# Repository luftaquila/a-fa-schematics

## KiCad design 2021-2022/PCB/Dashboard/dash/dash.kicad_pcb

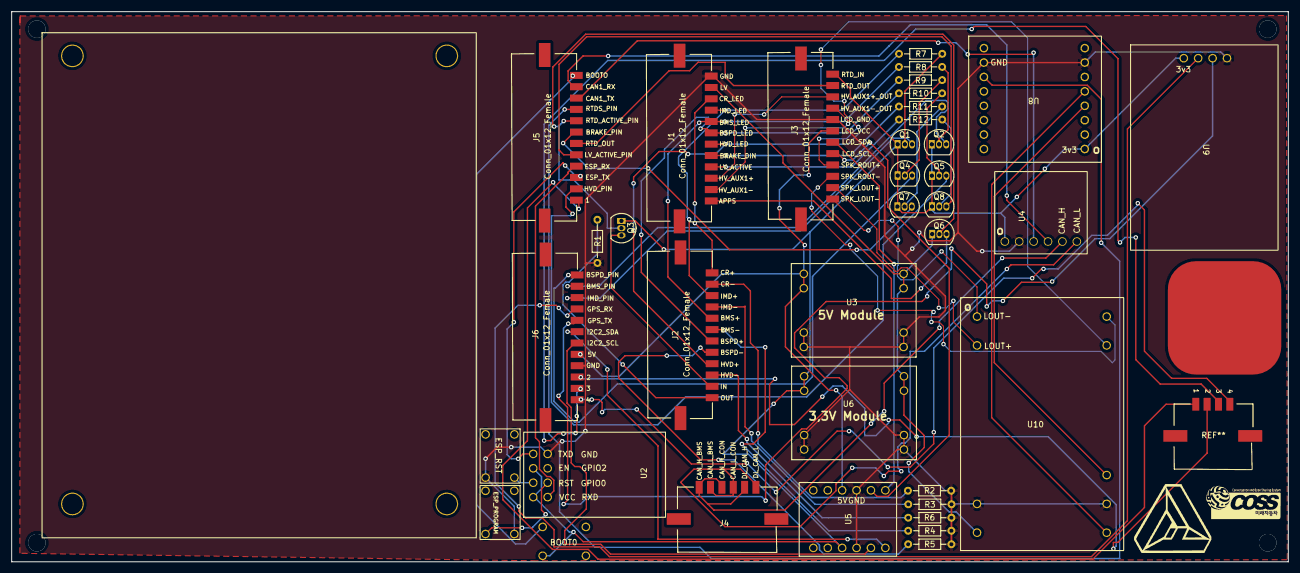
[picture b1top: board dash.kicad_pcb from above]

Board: 2 copper layers, 225.1 x 97.0 mm, 37 parts (0 on the bottom side), 56 nets.

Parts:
BOOT0: ESP_PROGRAM; butttttttttttttt
ESP_PROGRAM: ESP_PROGRAM; butttttttttttttt
ESP_RST: ESP_RST; butttttttttttttt
J1, J2, J3, J5, J6: Conn_01x12_Female; 5600201220
J4: Conn_01x06_Female; 6pin dura
Q1, Q2, Q3, Q4, Q5, Q6, Q7, Q8: 2N3904; TO-92_Inline
R1: 100; R_Axial_DIN0204_L3.6mm_D1.6mm_P7.62mm_Horizontal
R2, R3, R4, R5: 1k; R_Axial_DIN0204_L3.6mm_D1.6mm_P7.62mm_Horizontal
R6, R7, R8, R9, R10, R11, R12: 10k; R_Axial_DIN0204_L3.6mm_D1.6mm_P7.62mm_Horizontal
U2: ESP8266
U3, U6: DCDC_Module; DC CONVERTER
U4: CAN_TRANSCEIVER; SZH-EKBG-030
U5: LOGIC_LEVEL_CONVERTER; Logic Level Converter
U8: DFR0299
U9: NEO-7M
U10: D302; AUDIOIO

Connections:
3V3: BOOT0.1 (A), J3.1, Q1.1 (E), Q2.1 (E), Q3.1 (E), Q4.1 (E), Q5.1 (E), Q7.1 (E), Q8.1 (E), U2.1, U4.1, U5.1, U6.1 (VOUT+), U6.2 (VOUT+), U8.1, U9.1
5V: J3.6, J6.8, U3.1 (VOUT+), U3.2 (VOUT+), U5.1
-: J2.12, R1.2
APPS: J1.12, Q6.3 (C)
BMS-: J2.6, R4.1
BMS_IN: J1.5, J2.5, R8.1
BMS_Pin: J6.2, Q2.3 (C)
BOOT0: BOOT0.2 (B), J5.1
BRAKE_DIN: J1.8, R11.1
BRAKE_Pin: J5.6, Q7.3 (C)
BSPD-: J2.8, R5.1
BSPD_IN: J1.6, J2.7, R9.1
BSPD_Pin: J6.1, Q4.3 (C)
CAN1_RX: J5.2, U4.1
CAN1_TX: J5.3, U4.1
CAN_H: J4.1, J4.3, J4.5, U4.1
CAN_L: J4.2, J4.4, J4.6, U4.1
CR-: J2.2, R2.1
CRITICAL_LED: J1.3, J2.1
ESP_RX: J5.9, U2.1
ESP_TX: J5.10, U2.1
GND: ESP_PROGRAM.1 (A), ESP_RST.2 (B), J1.1, J3.5, J6.9, R1.1, R2.2, R3.2, R4.2, R5.2, R6.2, U2.1, U3.3 (VOUT-), U3.4 (VOUT-), U3.5 (VIN-), U3.6 (VIN-), U4.1, U5.1, U6.3 (VOUT-), U6.4 (VOUT-), U6.5 (VIN-), U6.6 (VIN-), U8.1, U9.1, U10.1
GPS_RX: J6.4, U9.1
GPS_TX: J6.5, U9.1
HVD-: J2.10, R6.1
HVD_IN: J1.7, J2.9, R10.1
HVD_Pin: J5.11, Q5.3 (C)
HV_AUX1+: J1.10, J3.3
HV_AUX1-: J1.11, J3.4
I2C2_SCL: J6.7, U5.1
I2C2_SDA: J6.6, U5.1
IMD-: J2.4, R3.1
IMD_IN: J1.4, J2.3, R7.1
IMD_Pin: J6.3, Q1.3 (C)
IN: J2.11, Q3.3 (C)
LCD_SCL: J3.8, U5.1
LCD_SDA: J3.7, U5.1
LIN: U8.1, U10.1
LOUT+: J3.11, U10.1
LOUT-: J3.12, U10.1
LV: J1.2, Q6.1 (E), U3.7 (VIN+), U3.8 (VIN+), U6.7 (VIN+), U6.8 (VIN+), U10.1
LV_ACTIVE: J1.9, R12.1
LV_ACTIVE_Pin: J5.8, Q8.3 (C)
unnamed: Q1.2 (B), R7.2
unnamed: Q2.2 (B), R8.2
unnamed: Q4.2 (B), R9.2
unnamed: Q5.2 (B), R10.2
unnamed: Q7.2 (B), R11.2
unnamed: Q8.2 (B), R12.2
unnamed: ESP_RST.1 (A), U2.1
unnamed: ESP_PROGRAM.2 (B), U2.1
RIN: U8.1, U10.1
ROUT+: J3.9, U10.1
ROUT-: J3.10, U10.1
RTDS: J5.4, U8.1
RTD_ACTIVE_Pin: J5.5, Q3.2 (B), Q6.2 (B)
RTD_OUT: J3.2, J5.7

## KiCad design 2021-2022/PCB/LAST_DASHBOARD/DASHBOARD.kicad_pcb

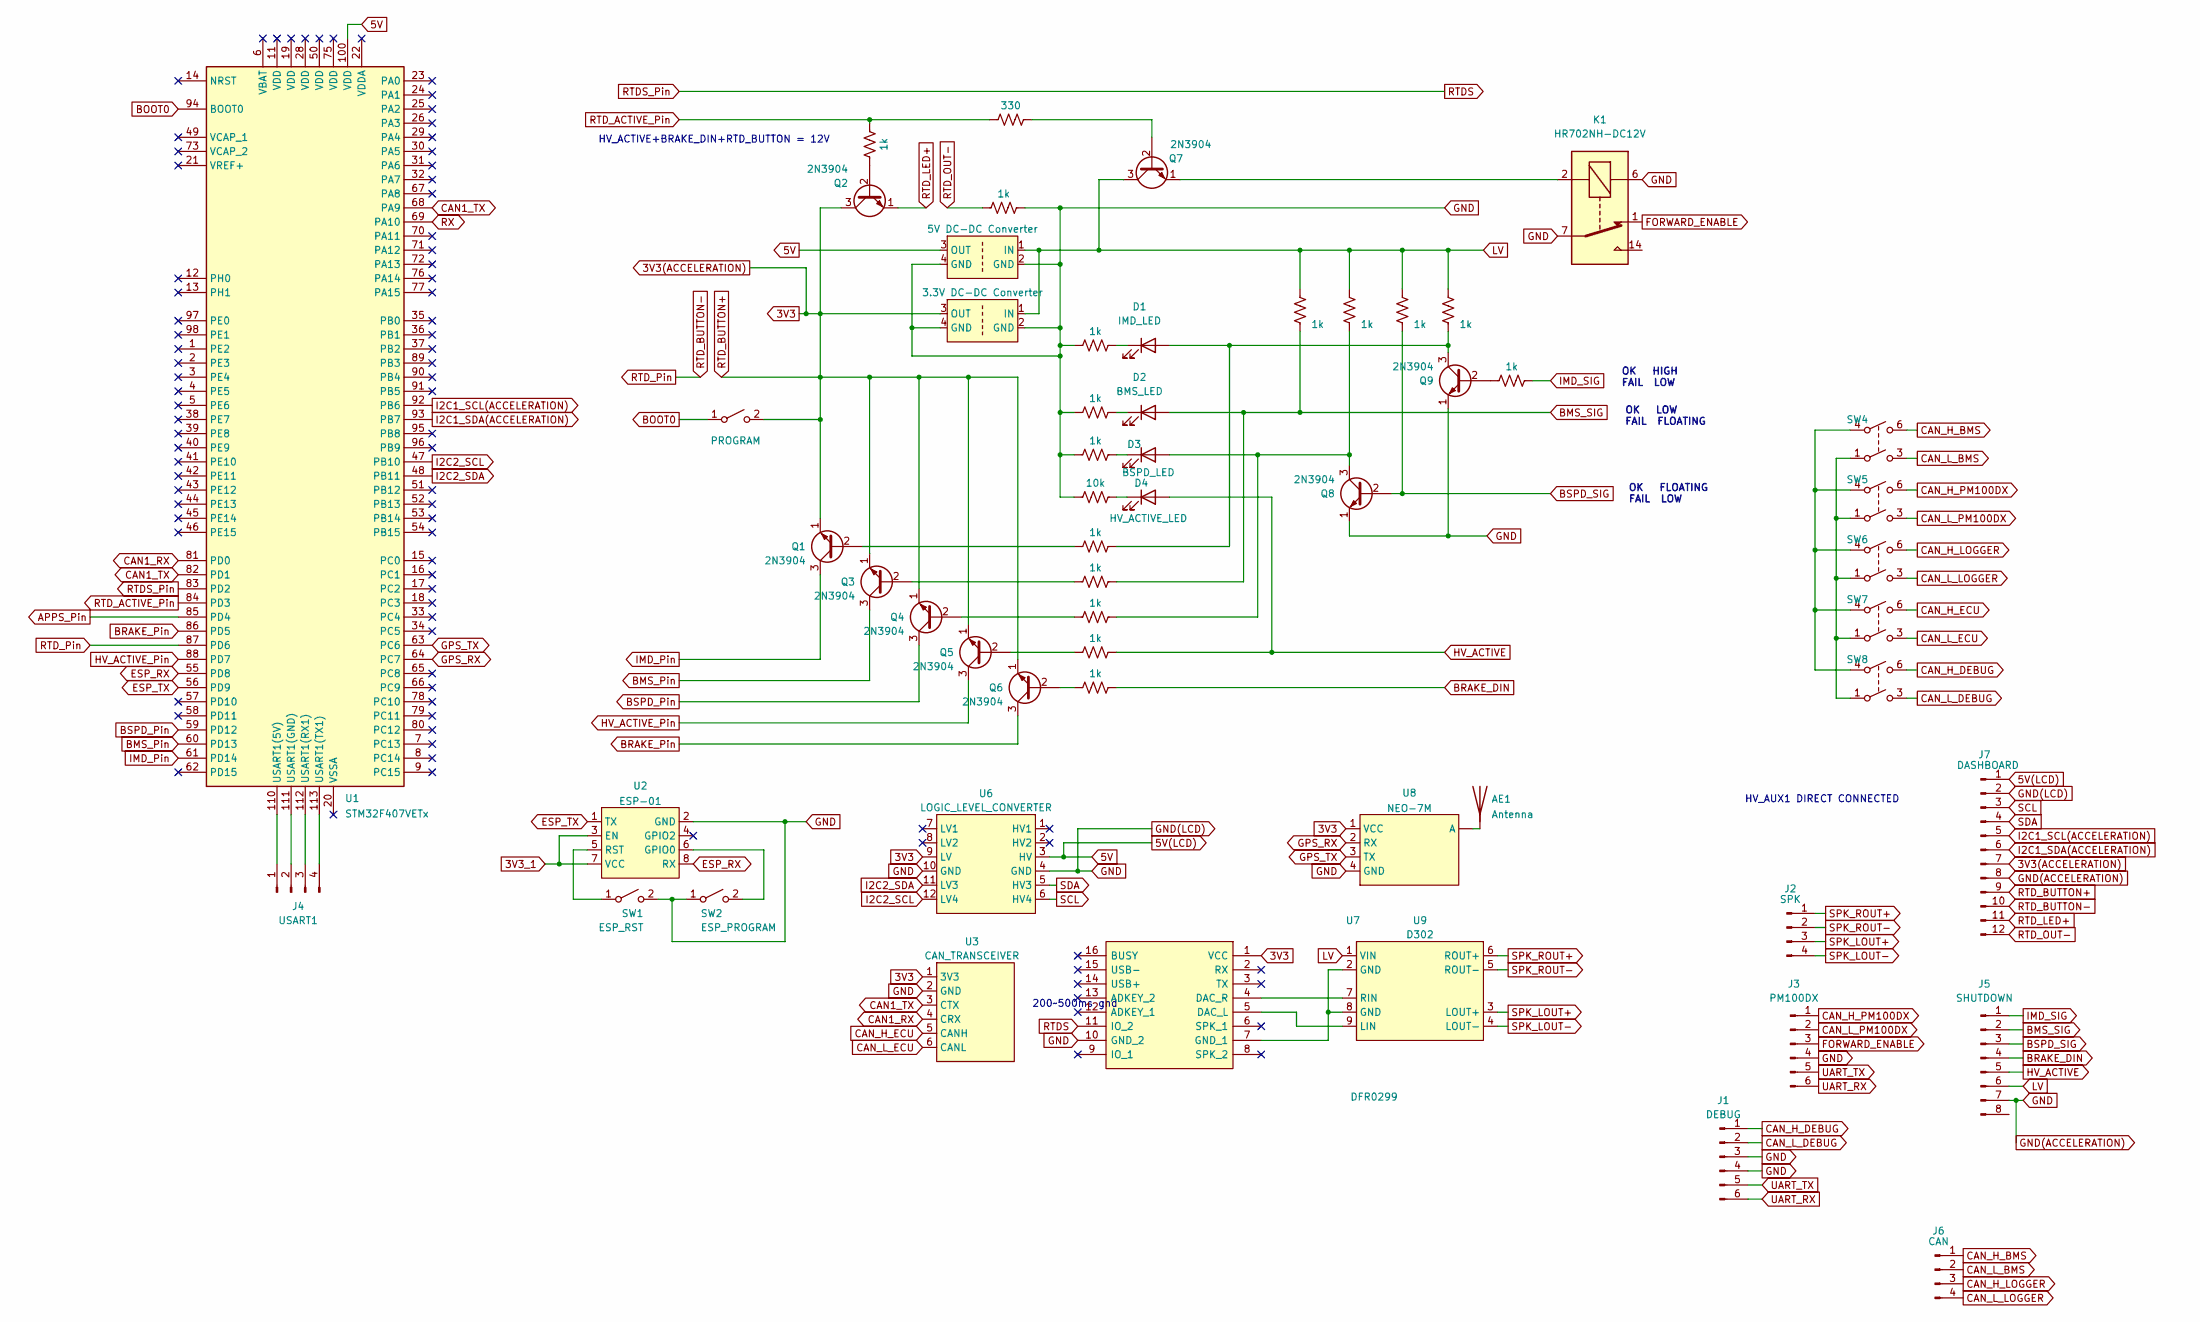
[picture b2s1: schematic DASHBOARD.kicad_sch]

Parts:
AE1: Antenna; ANTENA
D1: IMD_LED; LED_D5.0mm
D2: BMS_LED; LED_D5.0mm
D3: BSPD_LED; LED_D5.0mm
D4: HV_ACTIVE_LED; LED_D5.0mm
J1: DEBUG; PinHeader_1x06_P2.54mm_Vertical
J2: SPK; PinHeader_1x04_P2.54mm_Vertical
J3: PM100DX; PinHeader_1x06_P2.54mm_Vertical
J4: USART1; PinHeader_1x04_P2.54mm_Vertical
J5: SHUTDOWN; PinHeader_1x08_P2.54mm_Vertical
J6: CAN; PinHeader_1x04_P2.54mm_Vertical
J7: DASHBOARD; PinHeader_1x12_P2.54mm_Vertical
K1: HR702NH-DC12V
Q1, Q2, Q3, Q4, Q5, Q6, Q7, Q8, Q9: 2N3904; TO-92_Inline_Wide
R1, R2, R4, R5, R6, R8, R9, R10, R11, R12, R13, R14, R15, R16, R17: 1k; R_Axial_DIN0207_L6.3mm_D2.5mm_P10.16mm_Horizontal
R3: 330; R_Axial_DIN0207_L6.3mm_D2.5mm_P10.16mm_Horizontal
R7: 10k; R_Axial_DIN0207_L6.3mm_D2.5mm_P10.16mm_Horizontal
SW1: ESP_RST; TACT_SWITCH
SW2: ESP_PROGRAM; TACT_SWITCH
SW3: PROGRAM; TACT_SWITCH
SW4, SW5, SW6, SW7, SW8: SW_DPST; TOGGLE_SWITCH
U1: STM32F407VETx; STM32F407_HOLDER
U2: ESP-01; ESP01
U3: CAN_TRANSCEIVER; CAN_TRANSIVER
U4: 5V DC-DC Converter; DCDC_MODULE
U5: 3.3V DC-DC Converter; DCDC_MODULE
U6: LOGIC_LEVEL_CONVERTER
U7: DFR0299; Manufacturer_Part_Number DFR0299; Mouser Part Number 426-DFR0299
U8: NEO-7M; GPSV3-NE0
U9: D302; SFT-D302

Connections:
3V3: J7.7, J7.9, Q1.1 (E), Q2.3 (C), Q3.1 (E), Q4.1 (E), Q5.1 (E), Q6.1 (E), SW3.2 (B), U3.1 (3V3), U5.3 (OUT), U6.9 (LV), U7.1 (VCC), U8.1 (VCC)
3V3_1: U2.3 (EN), U2.7 (VCC)
5V: J7.1, U1.100 (VDD), U4.3 (OUT), U6.3 (HV)
APPS_Pin: U1.85 (PD4)
BMS_Pin: Q3.3 (C), U1.60 (PD13)
BMS_SIG: D2.2 (A), J5.2, R9.1, R13.2
BOOT0: SW3.1 (A), U1.94 (BOOT0)
BRAKE_DIN: J5.4, R12.1
BRAKE_Pin: Q6.3 (C), U1.86 (PD5)
BSPD_Pin: Q4.3 (C), U1.59 (PD12)
BSPD_SIG: J5.3, Q8.2 (B), R15.2
CAN1_RX: U1.81 (PD0), U3.4 (CRX)
CAN1_TX: U1.68 (PA9), U1.82 (PD1), U3.3 (CTX)
CAN_H_BMS: J6.1, SW4.6
CAN_H_DEBUG: J1.1, SW8.6
CAN_H_ECU: SW7.6, U3.5 (CANH)
CAN_H_LOGGER: J6.3, SW6.6
CAN_H_PM100DX: J3.1, SW5.6
CAN_L_BMS: J6.2, SW4.3
CAN_L_DEBUG: J1.2, SW8.3
CAN_L_ECU: SW7.3, U3.6 (CANL)
CAN_L_LOGGER: J6.4, SW6.3
CAN_L_PM100DX: J3.2, SW5.3
ESP_RX: U1.55 (PD8), U2.8 (RX)
ESP_TX: U1.56 (PD9), U2.1 (TX)
FORWARD_ENABLE: J3.3, K1.1
GND: J1.3, J1.4, J3.4, J5.7, J7.2, J7.8, K1.6, K1.7, K1.8, Q8.1 (E), Q9.1 (E), R2.1, R4.2, R5.2, R6.2, R7.2, SW1.2 (B), SW2.1 (A), U2.2 (GND), U3.2 (GND), U4.2 (GND), U4.4 (GND), U5.2 (GND), U5.4 (GND), U6.4 (GND), U6.10 (GND), U7.10 (GND_2), U8.4 (GND)
GPS_RX: U1.64 (PC7), U8.2 (RX)
GPS_TX: U1.63 (PC6), U8.3 (TX)
HV_ACTIVE: D4.2 (A), J5.5, R11.1
HV_ACTIVE_Pin: Q5.3 (C), U1.88 (PD7)
I2C1_SCL(ACCELERATION): J7.5, U1.92 (PB6)
I2C1_SDA(ACCELERATION): J7.6, U1.93 (PB7)
I2C2_SCL: U1.47 (PB10), U6.12 (LV4)
I2C2_SDA: U1.48 (PB11), U6.11 (LV3)
IMD_Pin: Q1.3 (C), U1.61 (PD14)
IMD_SIG: J5.1, R17.1
LV: J5.6, Q7.3 (C), R13.1, R14.1, R15.1, R16.1, U4.1 (IN), U5.1 (IN), U9.1 (VIN)
unnamed: AE1.1 (A), U8. (A)
unnamed: D1.1 (K), R4.1
unnamed: D1.2 (A), Q9.3 (C), R8.1, R16.2
unnamed: D2.1 (K), R5.1
unnamed: D3.1 (K), R6.1
unnamed: D3.2 (A), Q8.3 (C), R10.1, R14.2
unnamed: D4.1 (K), R7.1
unnamed: J4.1, U1.110 (USART1(5V))
unnamed: J4.2, U1.111 (USART1(GND))
unnamed: J4.3, U1.112 (USART1(RX1))
unnamed: J4.4, U1.113 (USART1(TX1))
unnamed: K1.2, Q7.1 (E)
unnamed: Q1.2 (B), R8.2
unnamed: Q2.2 (B), R1.1
unnamed: Q3.2 (B), R9.2
unnamed: Q4.2 (B), R10.2
unnamed: Q5.2 (B), R11.2
unnamed: Q6.2 (B), R12.2
unnamed: Q7.2 (B), R3.1
unnamed: Q9.2 (B), R17.2
unnamed: SW1.1 (A), U2.5 (RST)
unnamed: SW2.2 (B), U2.6 (GPIO0)
unnamed: SW4.1, SW5.1, SW6.1, SW7.1, SW8.1
unnamed: SW4.4, SW5.4, SW6.4, SW7.4, SW8.4
unnamed: U7.4 (DAC_R), U9.7 (RIN)
unnamed: U7.5 (DAC_L), U9.9 (LIN)
unnamed: U7.7 (GND_1), U9.2 (GND), U9.8 (GND)
RTDS: U1.83 (PD2), U7.11 (IO_2)
RTD_ACTIVE_Pin: R1.2, R3.2, U1.84 (PD3)
RTD_BUTTON-: J7.10, U1.87 (PD6)
RTD_LED+: J7.11, Q2.1 (E)
RTD_OUT-: J7.12, R2.2
RX: U1.69 (PA10)
SCL: J7.3, U6.6 (HV4)
SDA: J7.4, U6.5 (HV3)
SPK_LOUT+: J2.3, U9.3 (LOUT+)
SPK_LOUT-: J2.4, U9.4 (LOUT-)
SPK_ROUT+: J2.1, U9.6 (ROUT+)
SPK_ROUT-: J2.2, U9.5 (ROUT-)
UART_RX: J1.6, J3.6
UART_TX: J1.5, J3.5

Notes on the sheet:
OK HIGH FAIL LOW
HV_AUX1 DIRECT CONNECTED
200~500ms gnd
HV_ACTIVE+BRAKE_DIN+RTD_BUTTON = 12V
OK LOW FAIL FLOATING
OK FLOATING FAIL LOW

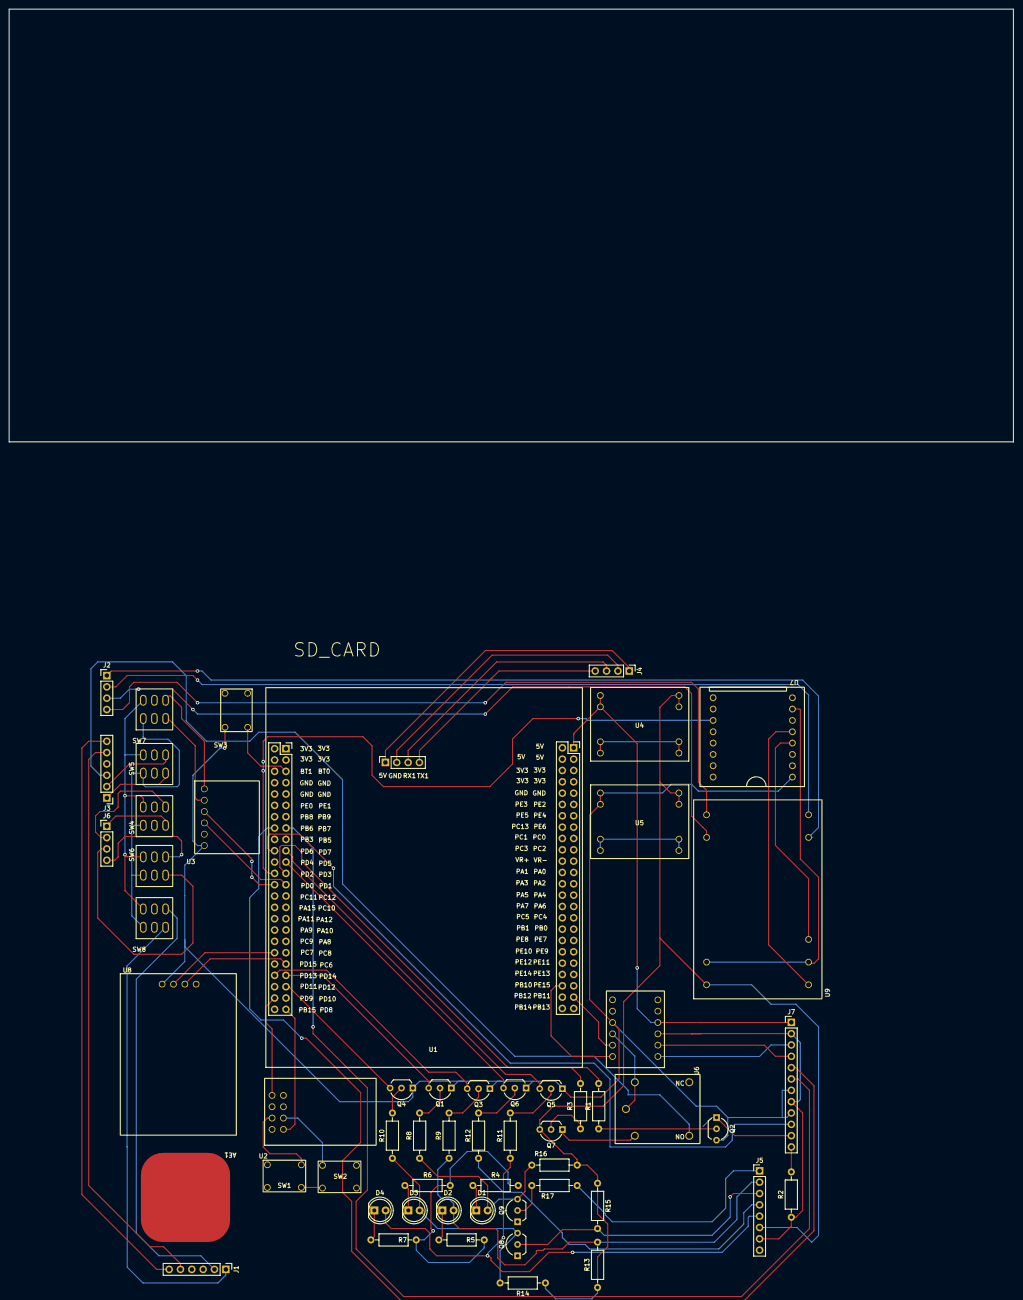
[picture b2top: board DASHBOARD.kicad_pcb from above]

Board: 2 copper layers, 225.1 x 97.0 mm, 56 parts (0 on the bottom side), 76 nets.

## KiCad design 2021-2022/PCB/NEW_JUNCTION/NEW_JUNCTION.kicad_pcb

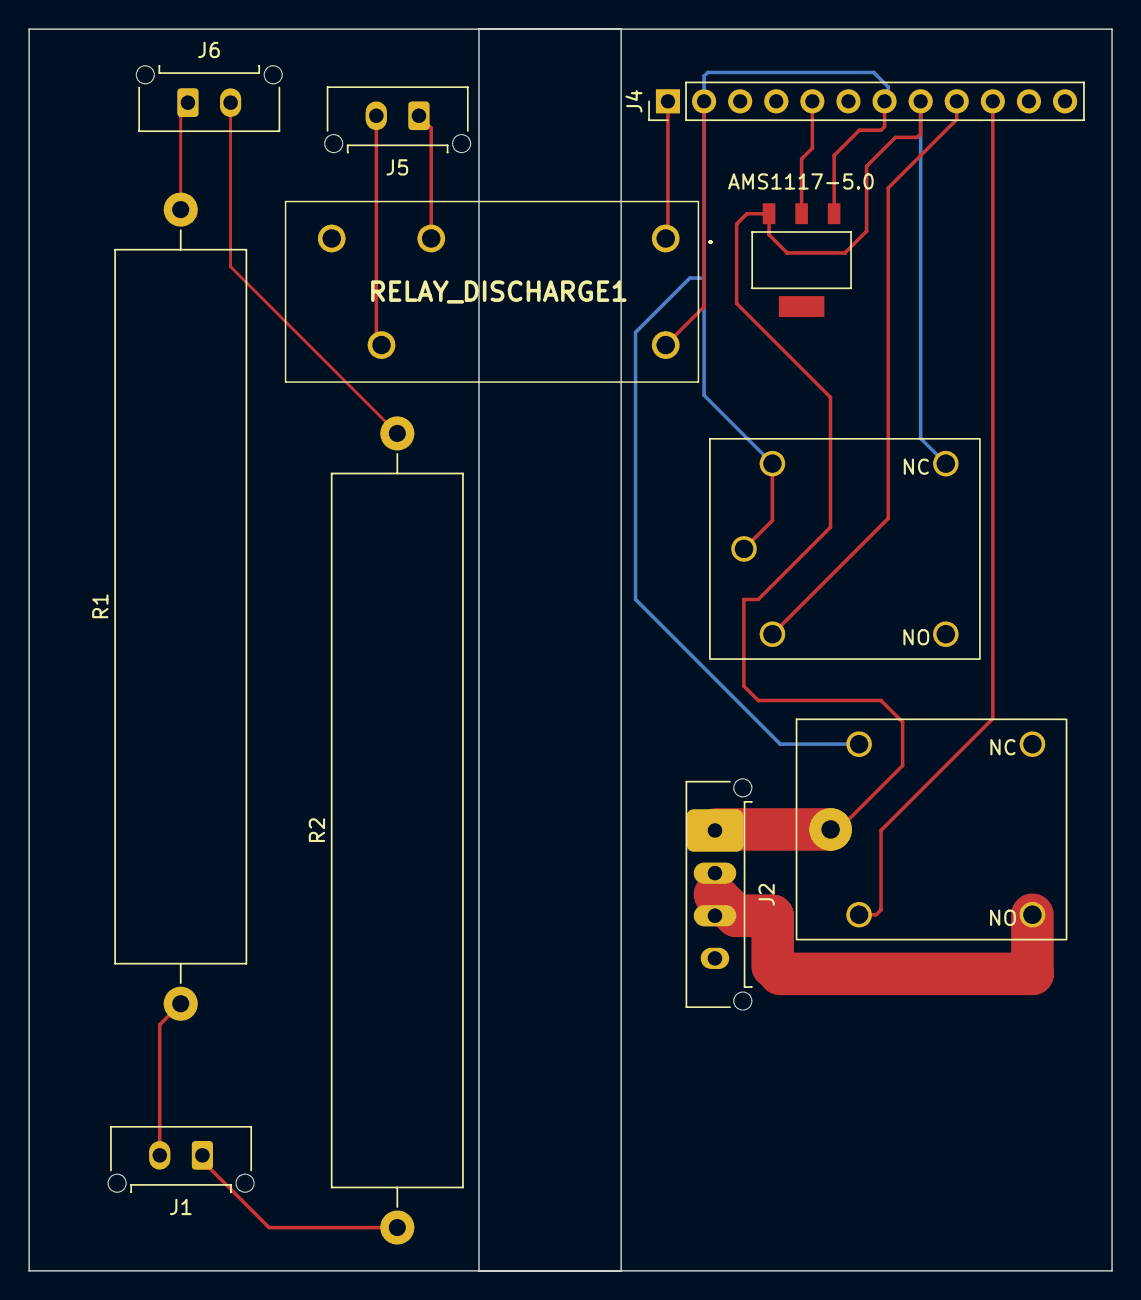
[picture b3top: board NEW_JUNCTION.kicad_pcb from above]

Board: 2 copper layers, 76.2 x 87.4 mm, 11 parts (0 on the bottom side), 14 nets.

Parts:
J1, J5: Conn_01x02_Male; Molex_Micro-Fit_3.0_43650-0215_1x02_P3.00mm_Vertical
J2: Conn_01x04_Male; Molex_Micro-Fit_3.0_43650-0415_1x04_P3.00mm_Vertical
J4: Conn_01x12_Male; PinHeader_1x12_P2.54mm_Vertical
J6: Conn_01x02_Female; Molex_Micro-Fit_3.0_43650-0215_1x02_P3.00mm_Vertical
K2, K3: HR702NH-DC12V
R1, R2: 10k; R_Axial_Power_L50.0mm_W9.0mm_P55.88mm
RELAY_DISCHARGE1: G2RL-1_12DC; G2RL112DC
U2: AMS1117-5.0

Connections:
5V_HALL: J4.5, U2.2 (VO)
FAN_PWR_LEFT: J2.2, J2.3, K3.1
GND_HALL: J4.2, J4.7, K2.6, K2.7, K3.6, RELAY_DISCHARGE1.5 (COIL_2), U2.1 (GND)
HV+: J5.1, RELAY_DISCHARGE1.2 (NC)
HV_ACTIVE_JNC: J4.1, RELAY_DISCHARGE1.1 (COIL_1)
LV_FAN: J2.1, K3.7, U2.3 (VI)
unnamed: J1.1, R2.1
unnamed: J1.2, R1.1
PUMP: J4.9, K2.2
PUMP_SIGNAL: J4.8, K2.14
RADIATOR_FAN: J4.10, K3.2
R_DISCHARGE: J5.2, RELAY_DISCHARGE1.4 (COM)
TSMP+: J6.1, R1.2
TSMP-: J6.2, R2.2

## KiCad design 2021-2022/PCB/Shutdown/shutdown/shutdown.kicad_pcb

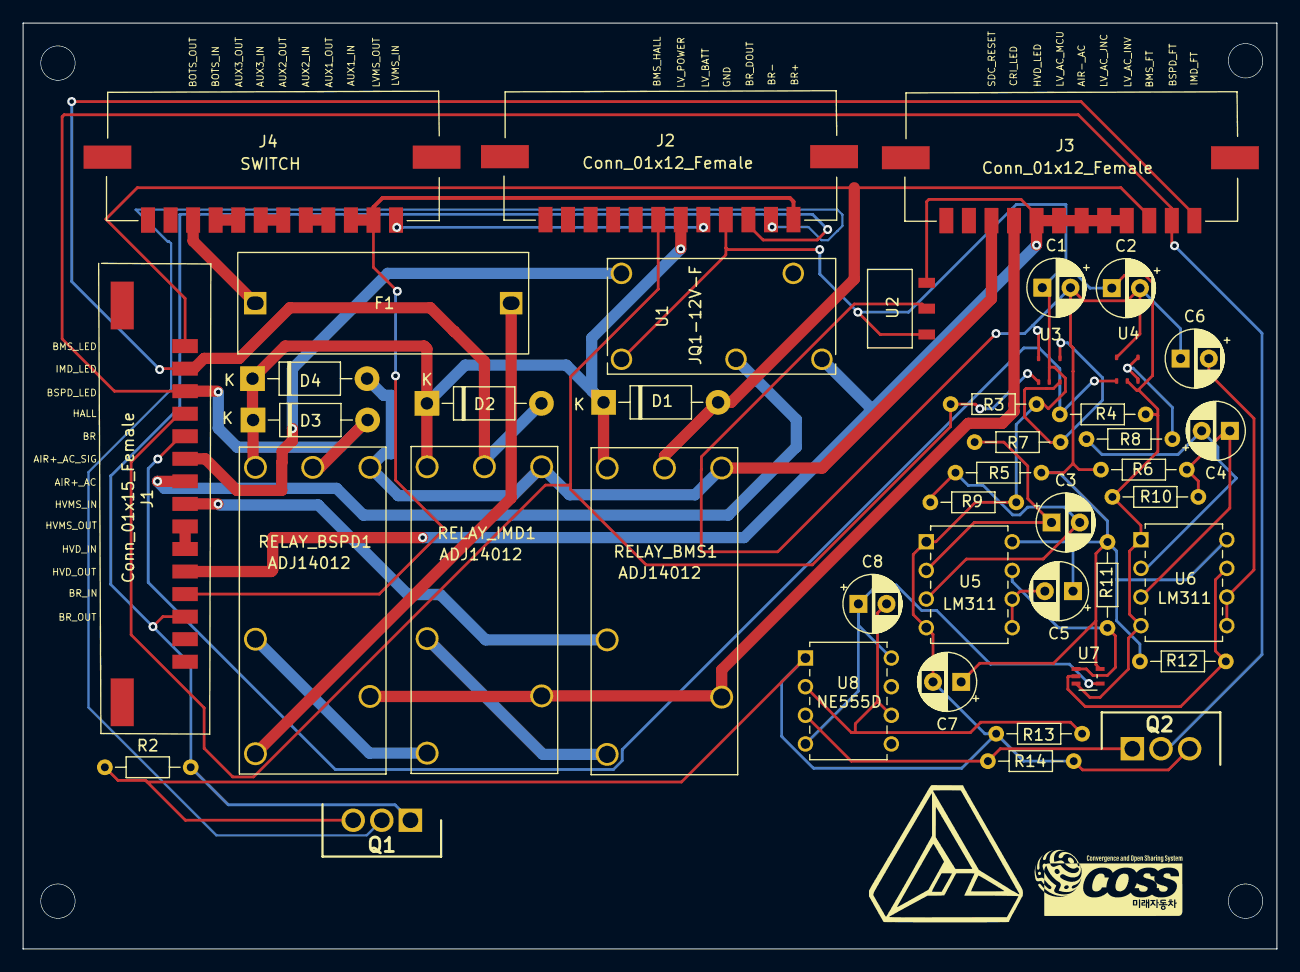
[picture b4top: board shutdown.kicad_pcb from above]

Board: 2 copper layers, 111.2 x 82.1 mm, 43 parts (0 on the bottom side), 39 nets.

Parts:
C1, C2, C7: 100nF; CP_Radial_D5.0mm_P2.50mm
C3, C4: 1nF; CP_Radial_D5.0mm_P2.50mm
C5, C6: 1uF; CP_Radial_D5.0mm_P2.50mm
C8: 10uF; CP_Radial_D5.0mm_P2.50mm
D1, D2, D3, D4: 1N4002; D_DO-41_SOD81_P10.16mm_Horizontal
F1: 4A Fuse; fuseholder
J1: Conn_01x15_Female; 5600201520
J2, J3: Conn_01x12_Female; 5600201220
J4: SWITCH; 5600201220
Q1, Q2: IRF640; irf640
R2, R3, R4, R11, R12, R14: 10k; R_Axial_DIN0204_L3.6mm_D1.6mm_P7.62mm_Horizontal
R5, R6: 4.7k; R_Axial_DIN0204_L3.6mm_D1.6mm_P7.62mm_Horizontal
R7, R8: 1k; R_Axial_DIN0204_L3.6mm_D1.6mm_P7.62mm_Horizontal
R9, R10: 5.2k; R_Axial_DIN0204_L3.6mm_D1.6mm_P7.62mm_Horizontal
R13: 62k; R_Axial_DIN0204_L3.6mm_D1.6mm_P7.62mm_Horizontal
RELAY_BMS1: ADJ14012
RELAY_BSPD1: ADJ14012
RELAY_IMD1: ADJ14012
U1: JQ1-12V-F
U2: AMS1117-5.0
U3, U4: BD77501G; BD77501G-TR
U5, U6: LM311; LM311P
U7: 74LVC1G08; 74LVC1G08GW_125
U8: NE555D; NE555P

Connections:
AIR+_ACTIVE: J1.7, U1.2
AIR+_ACTIVE_SIG: J1.6, U1.5
BMS_FAULT: D1.2 (A), J1.1, J3.3, RELAY_BMS1.9 (D)
BMS_HALL: J1.4, J2.7, R3.1, U3.1 (+)
BOTS_IN: J4.8, J4.9
BOTS_OUT: F1.1, J4.10
BRAKE: J1.5, R4.1, U4.1 (+)
BRAKE_DOUT: J1.13, J2.3, Q1.1 (G), R2.2
BRAKE_LIGHT-: J2.2, Q1.2 (D)
BSPD_FAULT: D3.2 (A), J1.3, J3.2, Q2.2 (D), RELAY_BSPD1.9 (D)
CRITICAL_LED: J3.9, RELAY_BMS1.6 (N), RELAY_BSPD1.6 (N), RELAY_IMD1.6 (N)
GND: C1.1, C2.1, C7.2, J2.4, Q1.3 (S), Q2.3 (S), R2.1, R3.2, R4.2, R9.1, R10.1, R13.2, R14.2, U1.1, U2.1 (GND), U3.2 (V-), U4.2 (V-), U5.1 (GND), U5.4 (V-), U6.1 (GND), U6.4 (V-), U7.3 (GND), U8.1 (GND)
HVD_INTERLOCK_IN: J1.9, J1.10
HVD_INTERLOCK_OUT: J1.11, J3.4, J3.5, J3.6, J3.7, J3.8, U1.3, U2.3 (VI)
HV_AUX2_IN: J4.4, J4.5
HV_AUX3_IN: J4.6, J4.7
HV_MASTER_IN: J1.8, RELAY_BMS1.2 (Out)
IMD_FAULT: D2.2 (A), J1.2, J3.1, RELAY_IMD1.9 (D)
LV_MASTER_IN: J2.5, J4.1
LV_MASTER_OUT: J1.12, J2.1, J4.2, J4.3
LV_POWER: D1.1 (K), D2.1 (K), D3.1 (K), D4.1 (K), J2.6, RELAY_BMS1.1 (V), RELAY_BSPD1.1 (V), RELAY_IMD1.1 (V)
unnamed: C3.1, R7.1, U5.2 (+)
unnamed: C3.2, R5.1, R9.2, U5.3 (-)
unnamed: C4.1, R6.1, R10.2, U6.3 (-)
unnamed: C4.2, R8.1, U6.2 (+)
unnamed: C5.2, U5.5 (BAL), U5.6 (STRB)
unnamed: C6.2, U6.5 (BAL), U6.6 (STRB)
unnamed: C8.1, U7.4, U8.4 (R), U8.8 (VCC)
unnamed: C8.2, R13.1, U8.2 (TR), U8.6 (THR)
unnamed: F1.2, RELAY_BSPD1.4 (12V)
unnamed: Q2.1 (G), R14.1, U8.3 (Q)
unnamed: R7.2, U3.3 (-), U3.4 (V+)
unnamed: R8.2, U4.3 (-), U4.4 (V+)
unnamed: R11.1, U5.7, U7.1
unnamed: R12.2, U6.7, U7.2
unnamed: RELAY_BMS1.4 (12V), RELAY_IMD1.2 (Out)
unnamed: RELAY_BSPD1.2 (Out), RELAY_IMD1.4 (12V)
SHUTDOWN_RESET: D4.2 (A), J3.10, RELAY_BMS1.8 (L), RELAY_BSPD1.8 (L), RELAY_IMD1.8 (L)
VCC: C1.2, C2.2, C5.1, C6.1, C7.1, R5.2, R6.2, R11.2, R12.1, U2.2 (VO), U3.5 (OUT), U4.5 (OUT), U5.8 (V+), U6.8 (V+), U7.5 (VCC)

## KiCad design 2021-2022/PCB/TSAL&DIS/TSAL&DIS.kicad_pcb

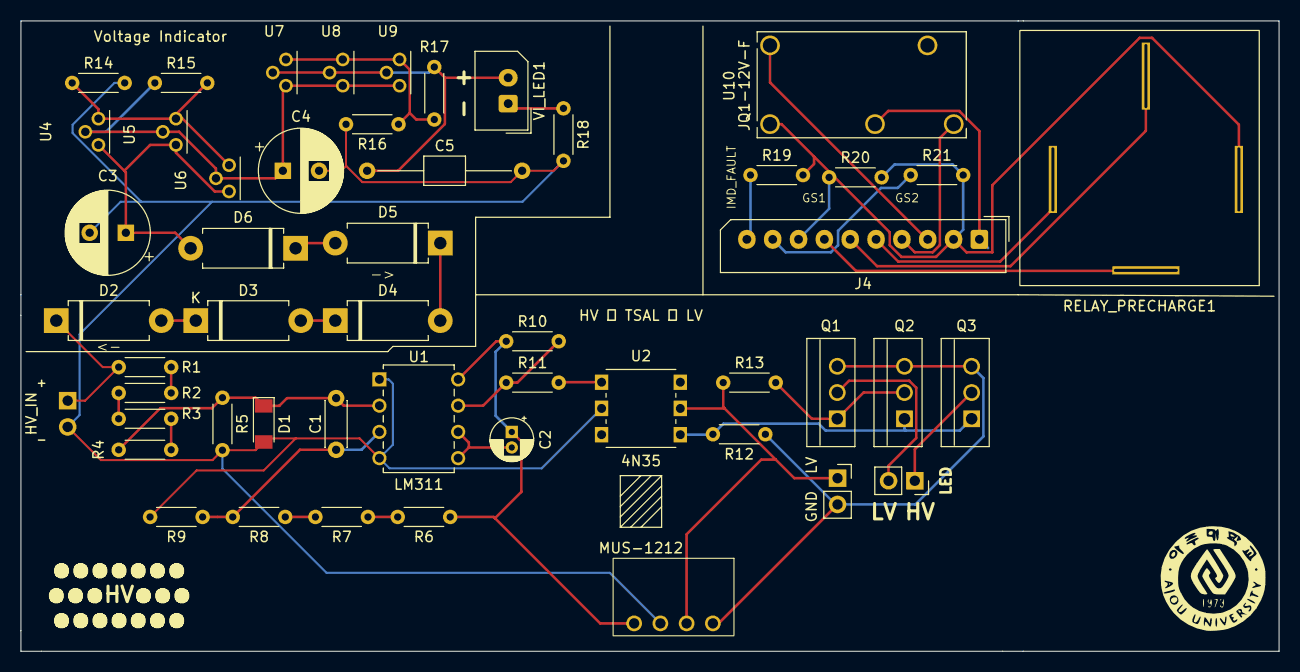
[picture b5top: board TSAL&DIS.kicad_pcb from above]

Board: 2 copper layers, 121.8 x 61.0 mm, 48 parts (0 on the bottom side), 35 nets.

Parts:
C1: 1nF; C_Disc_D4.3mm_W1.9mm_P5.00mm
C2: 1uF; CP_Radial_D4.0mm_P1.50mm
C3, C4: 2.2uF; CP_Radial_D8.0mm_P3.50mm
C5: 1uF; C_Axial_L3.8mm_D2.6mm_P15.00mm_Horizontal
D1: BZV55C12; D_MiniMELF
D2, D3, D4, D5, D6: 1N5349; D_DO-15_P10.16mm_Horizontal
J4: Conn_01x10_Female; Molex_SPOX_5267-10A_1x10_P2.50mm_Vertical
Q1, Q2, Q3: IRF640; IRF640NPBF
R1, R2, R3, R4, R6, R7, R8, R9: 4.7M; R_Axial_DIN0204_L3.6mm_D1.6mm_P5.08mm_Horizontal
R5: 1M; R_Axial_DIN0204_L3.6mm_D1.6mm_P5.08mm_Horizontal
R10, R13: 10k; R_Axial_DIN0204_L3.6mm_D1.6mm_P5.08mm_Horizontal
R11: 2k2; R_Axial_DIN0204_L3.6mm_D1.6mm_P5.08mm_Horizontal
R12: 100k; R_Axial_DIN0204_L3.6mm_D1.6mm_P5.08mm_Horizontal
R14, R16: 390k; R_Axial_DIN0204_L3.6mm_D1.6mm_P5.08mm_Horizontal
R15, R17: 4.7k; R_Axial_DIN0204_L3.6mm_D1.6mm_P5.08mm_Horizontal
R18: 1k; R_Axial_DIN0204_L3.6mm_D1.6mm_P5.08mm_Horizontal
R19, R20, R21: 2.2k; R_Axial_DIN0204_L3.6mm_D1.6mm_P5.08mm_Horizontal
RELAY_PRECHARGE1: V23700-C0001-A408; precharge-relay
U1: LM311; LM311P
U2: 4N35
U3: MUS-1212
U4, U5, U6, U7, U8, U9: LR8; LR8N3-G
U10: JQ1-12V-F
VI_LED1: 10mA; Molex_SPOX_5267-02A_1x02_P2.50mm_Vertical

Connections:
/HV+: D2.1 (K), R1.1
/HV-: C3.2, C4.2, C5.2, D1.2 (A), R5.2, R9.2, R14.2, R16.2, R18.2, U1.1 (GND), U1.4 (V-), U2.2, U3.3 (-Vout)
FAN+: J4.4, U10.3
FAN_ENABLE: J4.3, U10.5
GND: J4.2, Q1.3 (S), Q2.3 (S), Q3.3 (S), R12.1, R19.2, R20.2, R21.2, RELAY_PRECHARGE1.1, U3.1 (-Vin), U10.1
GND_SENSE1: J4.8, R20.1
GND_SENSE2: J4.9, R21.1
IMD_FAULT: J4.10, R19.1
LV: J4.1, R13.1, U2.5, U3.2 (+Vin), U10.2
unnamed: C1.1, R8.2, R9.1, U1.3 (-)
unnamed: C1.2, D1.1 (K), R4.2, R5.1, U1.2 (+)
unnamed: C2.1, R6.1, R10.1, U1.8 (V+), U3.4 (+Vout)
unnamed: C2.2, U1.5 (BAL), U1.6 (STRB)
unnamed: C3.1, D6.2 (A), U4.1 (IN), U5.1 (IN), U6.1 (IN)
unnamed: C4.1, R15.1, U4.2 (OUT), U5.2 (OUT), U6.2 (OUT), U7.1 (IN), U8.1 (IN), U9.1 (IN)
unnamed: C5.1, R17.1, U7.2 (OUT), U8.2 (OUT), U9.2 (OUT), VI_LED1.2 (A)
unnamed: D2.2 (A), D3.1 (K)
unnamed: D3.2 (A), D4.1 (K)
unnamed: D4.2 (A), D5.1 (K)
unnamed: D5.2 (A), D6.1 (K)
unnamed: Q1.1 (G), Q2.2 (D), R13.2
unnamed: Q2.1 (G), Q3.1 (G), R12.2, U2.4
unnamed: R1.2, R2.1
unnamed: R2.2, R3.1
unnamed: R3.2, R4.1
unnamed: R6.2, R7.1
unnamed: R7.2, R8.1
unnamed: R10.2, R11.1, U1.7
unnamed: R11.2, U2.1
unnamed: R14.1, R15.2, U4.3 (ADJ), U5.3 (ADJ), U6.3 (ADJ)
unnamed: R16.1, R17.2, U7.3 (ADJ), U8.3 (ADJ), U9.3 (ADJ)
unnamed: R18.1, VI_LED1.1 (K)
PRECHARGE: J4.5, RELAY_PRECHARGE1.2
RELAY_PRECHARGE: J4.6, RELAY_PRECHARGE1.3
R_PRECHARGE: J4.7, RELAY_PRECHARGE1.5

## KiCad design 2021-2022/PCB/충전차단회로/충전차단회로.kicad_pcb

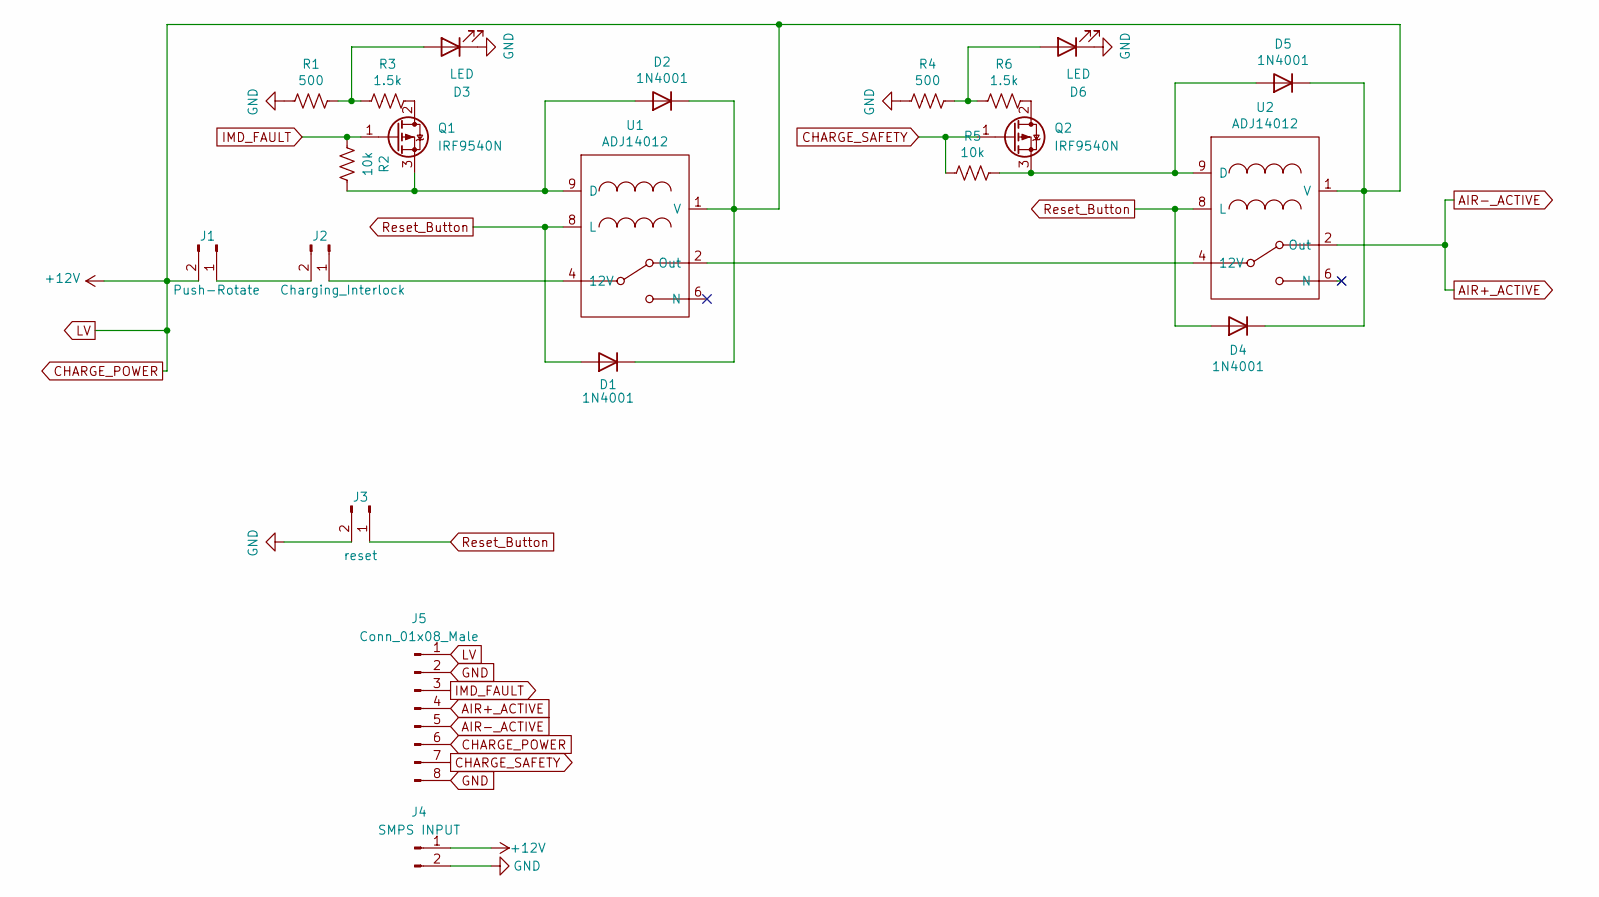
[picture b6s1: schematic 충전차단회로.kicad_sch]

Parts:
D1, D2, D4, D5: 1N4001; D_DO-15_P10.16mm_Horizontal
D3, D6: LED; LED_D5.0mm
J1: Push-Rotate; PinSocket_1x02_P2.54mm_Vertical
J2: Charging_Interlock; PinSocket_1x02_P2.54mm_Vertical
J3: reset; PinSocket_1x02_P2.54mm_Vertical
J4: SMPS INPUT; PinSocket_1x02_P2.54mm_Vertical
J5: Conn_01x08_Male; PinHeader_1x08_P2.54mm_Vertical
Q1, Q2: IRF9540N; TO-220-3_Vertical
R1, R4: 500; R_Axial_DIN0207_L6.3mm_D2.5mm_P10.16mm_Horizontal
R2, R5: 10k; R_Axial_DIN0207_L6.3mm_D2.5mm_P10.16mm_Horizontal
R3, R6: 1.5k; R_Axial_DIN0207_L6.3mm_D2.5mm_P10.16mm_Horizontal
U1, U2: ADJ14012

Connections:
AIR+_ACTIVE: J5.4, J5.5, U2.2 (Out)
CHARGE_POWER: D1.1 (K), D2.1 (K), D4.1 (K), D5.1 (K), J1.2, J4.1, J5.1, J5.6, U1.1 (V), U2.1 (V)
CHARGE_SAFETY: J5.7, Q2.1 (G), R5.2
GND: D3.1 (K), D6.1 (K), J3.2, J4.2, J5.2, J5.8, R1.2, R4.2
IMD_FAULT: J5.3, Q1.1 (G), R2.2
unnamed: D2.2 (A), Q1.3 (S), R2.1, U1.9 (D)
unnamed: D3.2 (A), R1.1, R3.2
unnamed: D5.2 (A), Q2.3 (S), R5.1, U2.9 (D)
unnamed: D6.2 (A), R4.1, R6.2
unnamed: J1.1, J2.2
unnamed: J2.1, U1.4 (12V)
unnamed: Q1.2 (D), R3.1
unnamed: Q2.2 (D), R6.1
unnamed: U1.2 (Out), U2.4 (12V)
Reset_Button: D1.2 (A), D4.2 (A), J3.1, U1.8 (L), U2.8 (L)

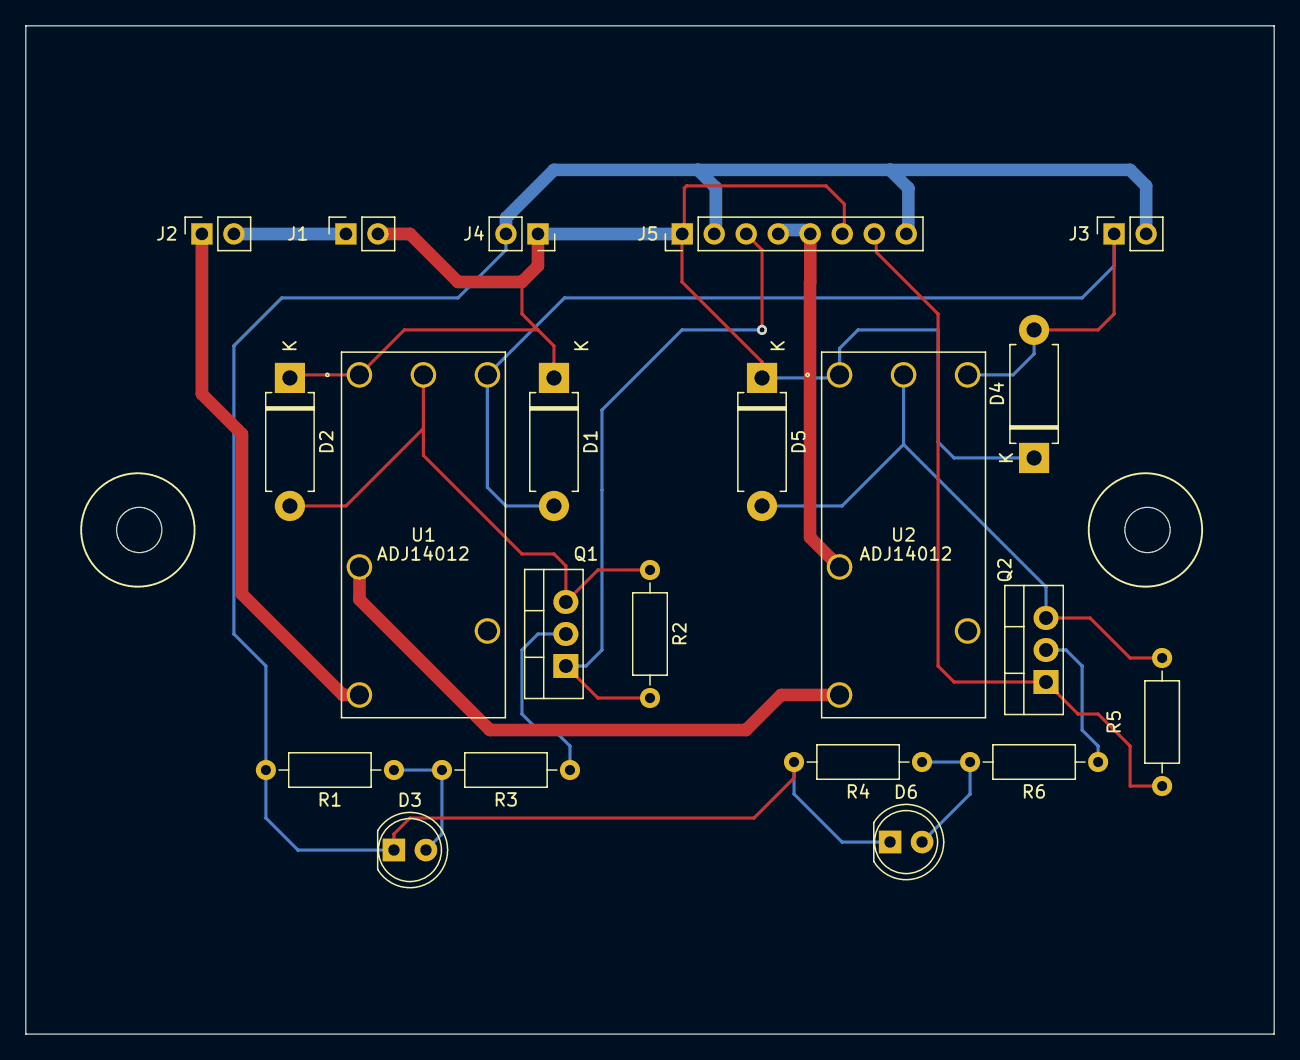
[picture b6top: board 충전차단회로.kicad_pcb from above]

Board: 2 copper layers, 99.1 x 80.0 mm, 21 parts (0 on the bottom side), 15 nets.

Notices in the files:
parts and their libraries:
Copyright 2021 Accelerated Designs. All rights reserved.
